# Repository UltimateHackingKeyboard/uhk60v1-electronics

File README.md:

Ultimate Hacking Keyboard electronics
=====================================

Contained are the schematics and board layout KiCad files for the [Ultimate Hacking Keyboard](https://ultimatehackingkeyboard.com/).

Please make sure to clone this repo with:

`git clone --recursive https://github.com/UltimateHackingKeyboard/uhk60v1-electronics.git`

Now, you should be able to open any of the 4 [KiCad](https://kicad.org/) projects of the repo:

* [left-main](left-main) contains main PCB of left keyboard half.
* [right-main](right-main) contains the main PCB of the right keyboard half.
* [display](display) contains the PCB that interfaces our custom manufactured LED segment display with the left main PCB.
* [connectors](connectors) are very small PCBs that are soldered vertically to the left and right main circuit boards to interconnect the keyboard halves without needing a bridge cable.

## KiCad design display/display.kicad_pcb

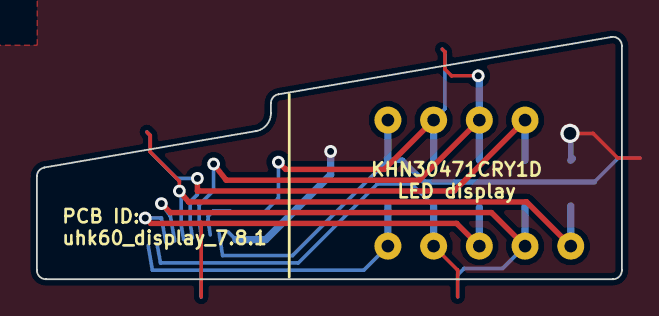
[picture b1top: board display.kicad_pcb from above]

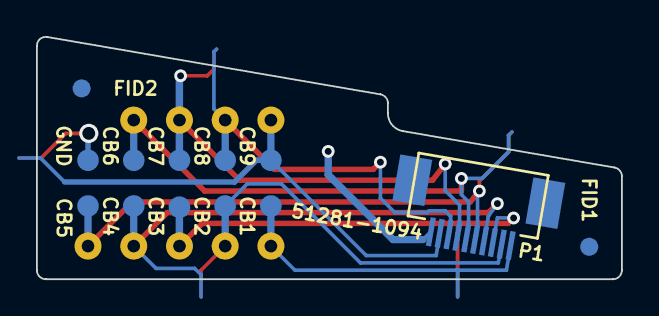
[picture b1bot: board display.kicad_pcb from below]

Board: 2 copper layers, 32.5 x 13.5 mm, 14 parts (13 on the bottom side), 10 nets.

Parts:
FID1, FID2: FIDUCIAL; FID
P1: 51281-1094; FFC_Connector_51281-1094
P2: CONN_9; UHK_LED_display
TP_CB1: CB1; Test_Point
TP_CB2: CB2; Test_Point
TP_CB3: CB3; Test_Point
TP_CB4: CB4; Test_Point
TP_CB5: CB5; Test_Point
TP_CB6: CB6; Test_Point
TP_CB7: CB7; Test_Point
TP_CB8: CB8; Test_Point
TP_CB9: CB9; Test_Point
TP_GND1: GND; Test_Point

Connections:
/CB1: P1.1, P2.1, TP_CB1.1
/CB2: P1.2, P2.2, TP_CB2.1
/CB3: P1.3, P2.3, TP_CB3.1
/CB4: P1.4, P2.4, TP_CB4.1
/CB5: P1.5, P2.5, TP_CB5.1
/CB6: P1.6, P2.6, TP_CB6.1
/CB7: P1.7, P2.7, TP_CB7.1
/CB8: P1.8, P2.8, TP_CB8.1
/CB9: P1.9, P2.9, TP_CB9.1
GND: P1.10, TP_GND1.1

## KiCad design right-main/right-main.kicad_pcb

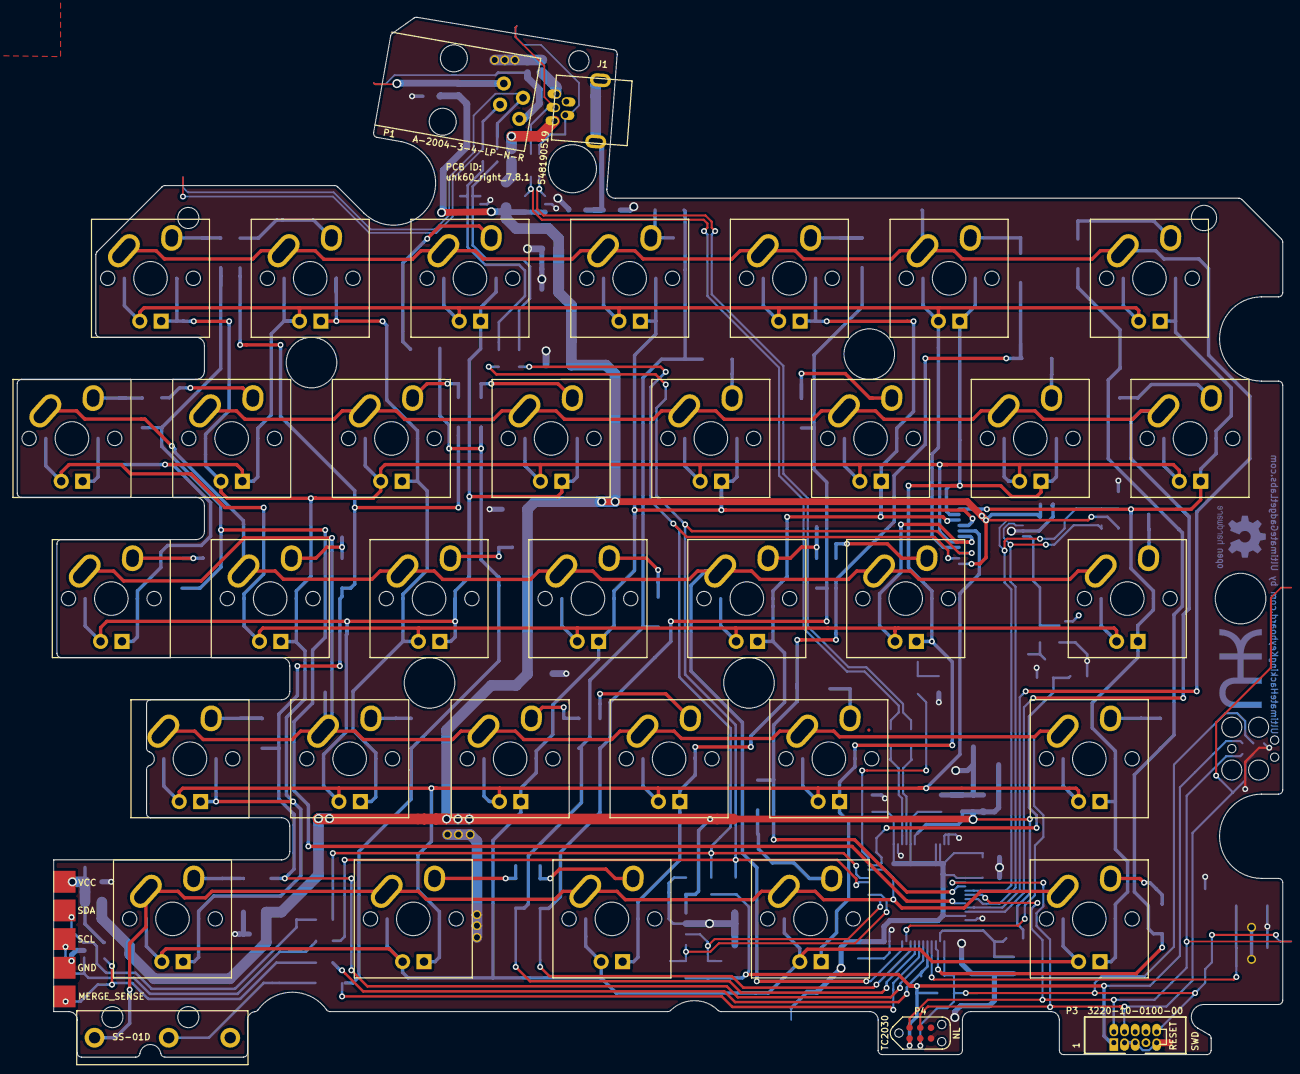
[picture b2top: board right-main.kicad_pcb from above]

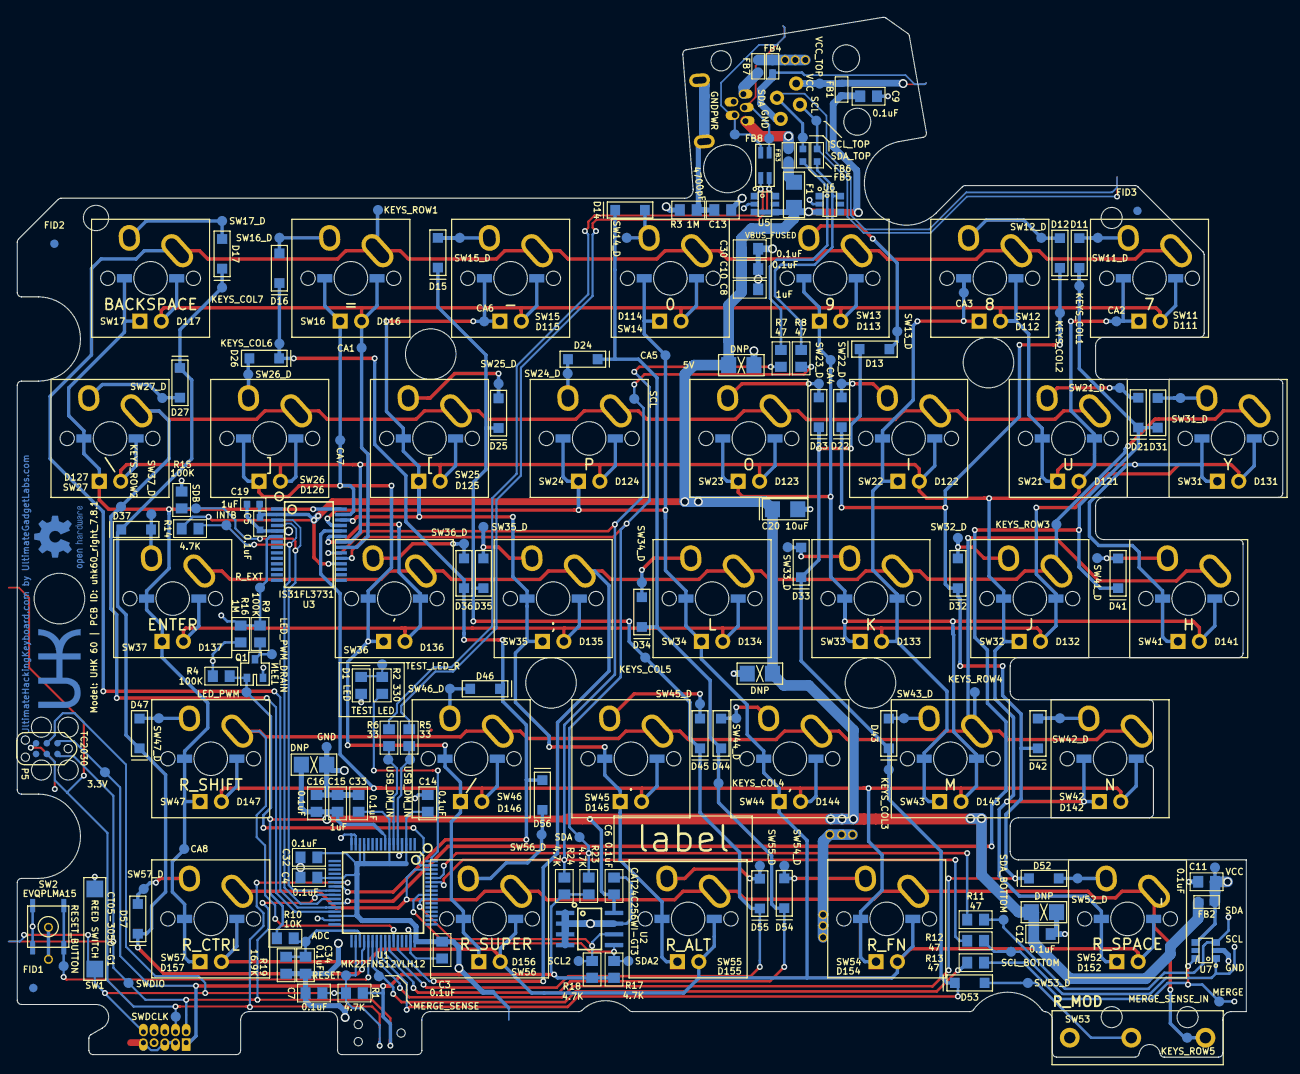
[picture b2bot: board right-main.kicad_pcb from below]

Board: 2 copper layers, 150.1 x 123.4 mm, 285 parts (224 on the bottom side), 94 nets.

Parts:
C3, C4, C6, C7, C9, C10, C11, C12, C14, C16, C30, C32, C33, C34: 0.1uF; SM0805
C5: 0.1uF; SM0603
C8, C15: 1uF; SM0805
C13: 4700pF; SM0805
C19: 1uF; SM0603
C20: 10uF; SM1206_Diode
C22, C23, C24, C25: DNP; SM1206_DNP
D1: LED; SM0805_Diode
D11, D12, D13, D14, D15, D16, D17, D21, D22, D23, D24, D25, D26, D27, D31, D32, D33, D34, D35, D36, D37, D41, D42, D43, D44, D45, D46, D47, D52, D53, D54, D55, D56, D57: DIODE; SOD-123_Diode
D111, D112, D113, D114, D115, D116, D117, D121, D122, D123, D124, D125, D126, D127, D131, D132, D133, D134, D135, D136, D137, D141, D142, D143, D144, D145, D146, D147, D152, D154, D155, D156, D157: LED; Cherry_MX_LED
F1: FUSE; SM1206
FB1, FB2, FB3, FB4, FB5, FB6, FB7: FERRITE_BEAD; SM0603
FB8: FERRITE_BEAD_COMMON_MODE; Wurth_744232090
FID1, FID2, FID3: >VALUE; FID
G1: LOGO; UHK_Logo_5mm_height
G2: LOGO; OSHW_Logo_6mm_height_BCu
GndVia1, GndVia2, GndVia3, GndVia4, GndVia5, GndVia6, GndVia7, GndVia8, GndVia9: VIA; via_28_42mil_solid_con
J1: 548190519; USB_Mini_B_Connector_0548190519
LABEL1: label
P1: A-2004-3-4-LP-N-R; 4P4C_Jack_A-2004-3-4-LP-N-R
P2: CONN_5; UHK_Connector_Right_PCB
P3: 3220-10-0100-00; 2x5_0.05_pitch_pin_shrouded_header_min
P4: CONN_6; Tag_Connect_2x3_Header_No_Legs
P5: CONN_6; Tag_Connect_2x3_Header_With_Legs
Q1: MOSFET_N; SOT-23-GSD
R1, R14, R17, R18, R23, R24: 4.7K; SM0805
R2: 330; SM0805
R3, R16: 1M; SM0805
R4, R9, R15: 100K; SM0805
R5, R6: 33; SM0805
R7, R8, R11, R12, R13: 47; SM0805
R10: 10K; SM0805
R19: 16.9K; SM0805
SW1: CT05-3050-G1; Reed_Switch_CT05-3050-G1
SW2: EVQPLMA15
SW11: 7; Cherry_MX_Matias_Hybrid
SW12: 8; Cherry_MX_Matias_Hybrid
SW13: 9; Cherry_MX_Matias_Hybrid
SW14: 0; Cherry_MX_Matias_Hybrid
SW15: -; Cherry_MX_Matias_Hybrid
SW16: =; Cherry_MX_Matias_Hybrid
SW17: BACKSPACE; Cherry_MX_Matias_Hybrid
SW21: U; Cherry_MX_Matias_Hybrid
SW22: I; Cherry_MX_Matias_Hybrid
SW23: O; Cherry_MX_Matias_Hybrid
SW24: P; Cherry_MX_Matias_Hybrid
SW25: [; Cherry_MX_Matias_Hybrid
SW26: ]; Cherry_MX_Matias_Hybrid
SW27: \; Cherry_MX_Matias_Hybrid
SW31: Y; Cherry_MX_Matias_Hybrid
SW32: J; Cherry_MX_Matias_Hybrid
SW33: K; Cherry_MX_Matias_Hybrid
SW34: L; Cherry_MX_Matias_Hybrid
SW35: ;; Cherry_MX_Matias_Hybrid
SW36: '; Cherry_MX_Matias_Hybrid
SW37: ENTER; Cherry_MX_Matias_Hybrid
SW41: H; Cherry_MX_Matias_Hybrid
SW42: N; Cherry_MX_Matias_Hybrid_Right_Pin
SW43: M; Cherry_MX_Matias_Hybrid
SW44: ,; Cherry_MX_Matias_Hybrid
SW45: .; Cherry_MX_Matias_Hybrid
SW46: /; Cherry_MX_Matias_Hybrid
SW47: R_SHIFT; Cherry_MX_Matias_Hybrid
SW52: R_SPACE; Cherry_MX_Matias_Hybrid
SW53: R_MOD; SS-01D
SW54: R_FN; Cherry_MX_Matias_Hybrid
SW55: R_ALT; Cherry_MX_Matias_Hybrid
SW56: R_SUPER; Cherry_MX_Matias_Hybrid
SW57: R_CTRL; Cherry_MX_Matias_Hybrid
TP_3.3V1: 3.3V; Test_Point
TP_5V1: 5V; Test_Point
TP_ADC1: ADC; Test_Point
TP_CA1: CA1; Test_Point
TP_CA2: CA2; Test_Point
TP_CA3: CA3; Test_Point
TP_CA4: CA4; Test_Point
TP_CA5: CA5; Test_Point
TP_CA6: CA6; Test_Point
TP_CA7: CA7; Test_Point
TP_CA8: CA8; Test_Point
TP_GND1: GND; Test_Point
TP_GNDPWR1: GNDPWR; Test_Point
TP_INTB1: INTB; Test_Point
TP_KEYS_COL1: KEYS_COL1; Test_Point
TP_KEYS_COL2: KEYS_COL2; Test_Point
TP_KEYS_COL3: KEYS_COL3; Test_Point
TP_KEYS_COL4: KEYS_COL4; Test_Point
TP_KEYS_COL5: KEYS_COL5; Test_Point
TP_KEYS_COL6: KEYS_COL6; Test_Point
TP_KEYS_COL7: KEYS_COL7; Test_Point
TP_KEYS_ROW1: KEYS_ROW1; Test_Point
TP_KEYS_ROW2: KEYS_ROW2; Test_Point
TP_KEYS_ROW3: KEYS_ROW3; Test_Point
TP_KEYS_ROW4: KEYS_ROW4; Test_Point
TP_KEYS_ROW5: KEYS_ROW5; Test_Point
TP_LED_PWM1: LED_PWM; Test_Point
TP_LED_PWM_DRAIN1: LED_PWM_DRAIN; Test_Point
TP_MERGE_SENSE1: MERGE_SENSE; Test_Point
TP_MERGE_SENSE_IN1: MERGE_SENSE_IN; Test_Point
TP_RESET1: RESET; Test_Point
TP_RESET_BUTTON1: RESET_BUTTON; Test_Point
TP_R_EXT1: R_EXT; Test_Point
TP_SCL1: SCL; Test_Point
TP_SCL2: SCL2; Test_Point
TP_SCL_BOTTOM1: SCL_BOTTOM; Test_Point
TP_SCL_TOP1: SCL_TOP; Test_Point
TP_SDA1: SDA; Test_Point
TP_SDA2: SDA2; Test_Point
TP_SDA_BOTTOM1: SDA_BOTTOM; Test_Point
TP_SDA_TOP1: SDA_TOP; Test_Point
TP_SDB1: SDB; Test_Point
TP_SW11_D1: SW11_D; Test_Point
TP_SW12_D1: SW12_D; Test_Point
TP_SW13_D1: SW13_D; Test_Point
TP_SW14_D1: SW14_D; Test_Point
TP_SW15_D1: SW15_D; Test_Point
TP_SW16_D1: SW16_D; Test_Point
TP_SW17_D1: SW17_D; Test_Point
TP_SW21_D1: SW21_D; Test_Point
TP_SW22_D1: SW22_D; Test_Point
TP_SW23_D1: SW23_D; Test_Point
TP_SW24_D1: SW24_D; Test_Point
TP_SW25_D1: SW25_D; Test_Point
TP_SW26_D1: SW26_D; Test_Point
TP_SW27_D1: SW27_D; Test_Point
TP_SW31_D1: SW31_D; Test_Point
TP_SW32_D1: SW32_D; Test_Point
TP_SW33_D1: SW33_D; Test_Point
TP_SW34_D1: SW34_D; Test_Point
TP_SW35_D1: SW35_D; Test_Point
TP_SW36_D1: SW36_D; Test_Point
TP_SW37_D1: SW37_D; Test_Point
TP_SW41_D1: SW41_D; Test_Point
TP_SW42_D1: SW42_D; Test_Point
TP_SW43_D1: SW43_D; Test_Point
TP_SW44_D1: SW44_D; Test_Point
TP_SW45_D1: SW45_D; Test_Point
TP_SW46_D1: SW46_D; Test_Point
TP_SW47_D1: SW47_D; Test_Point
TP_SW52_D1: SW52_D; Test_Point
TP_SW53_D1: SW53_D; Test_Point
TP_SW54_D1: SW54_D; Test_Point
TP_SW55_D1: SW55_D; Test_Point
TP_SW56_D1: SW56_D; Test_Point
TP_SW57_D1: SW57_D; Test_Point
TP_SWDCLK1: SWDCLK; Test_Point
TP_SWDIO1: SWDIO; Test_Point
TP_TEST_LED_R1: TEST_LED_R; Test_Point
TP_USB_DM1: USB_DM_IN; Test_Point
TP_USB_DM_IN1: USB_DM_IN; Test_Point
TP_USB_DP1: USB_DM_IN; Test_Point
TP_USB_DP_IN1: USB_DP_IN; Test_Point
TP_VBUS_FUSED1: VBUS_FUSED; Test_Point
TP_VCC_BOTTOM1: VCC_BOTTOM; Test_Point
TP_VCC_TOP1: VCC_TOP; Test_Point
U1: MK22FN512VLH12; LQFP64
U2: CAT24C256WI-GT3; EEPROM-SOIC8
U3: IS31FL3731; SSOP-28
U5, U6, U7: ESD; SC-74-TVS
VIA1, VIA2: via_28_42mil_solid_con
hole: 2.6mm; hole_2.4mm
hole#2, hole#3, hole#4, hole#5, hole#6: 6mm; hole_6mm
hole#7: 5.7mm; hole_5.7mm
hole#8, hole#10, hole#11: 2.5mm; hole_2.5mm
hole#9: 3mm; hole_3mm

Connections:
+3V3: C3.2, C4.1, C14.2, C32.2, C33.2, P3.1, P4.1, P5.1, R1.1, R17.1, R18.1, R23.1, R24.1, TP_3.3V1.1, U1.3, U1.7, U1.13, U1.14, U1.21, U1.30, U1.48
+5V: C5.2, C6.2, C8.2, C9.2, C10.2, C12.2, C15.2, C16.2, C19.2, C20.1, C22.2, C23.2, C24.2, C25.2, C30.2, F1.1, FB1.2, FB2.2, R10.1, R14.1, TP_5V1.1, TP_VBUS_FUSED1.1, U1.8, U2.8, U3.2, U3.18, U5.3, U5.4, U6.3
/ADC: C34.2, R10.2, R19.1, TP_ADC1.1, U1.35
/CA1: D111.2, D112.2, D113.2, D114.2, D115.2, D116.2, D117.2, D121.1, D131.1, D141.1, TP_CA1.1, U3.21
/CA2: D111.1, D121.2, D122.2, D123.2, D124.2, D125.2, D126.2, D127.2, D132.1, D142.1, D152.1, TP_CA2.1, U3.22
/CA3: D112.1, D122.1, D131.2, D132.2, D133.2, D134.2, D135.2, D136.2, D137.2, D143.1, TP_CA3.1, U3.23
/CA4: D113.1, D123.1, D133.1, D141.2, D142.2, D143.2, D144.2, D145.2, D146.2, D147.2, D154.1, TP_CA4.1, U3.24
/CA5: D114.1, D124.1, D134.1, D144.1, D152.2, D154.2, D155.2, D156.2, D157.2, TP_CA5.1, U3.25
/CA6: D115.1, D125.1, D135.1, D145.1, D155.1, TP_CA6.1, U3.26
/CA7: D116.1, D126.1, D136.1, D146.1, D156.1, TP_CA7.1, U3.27
/CA8: D117.1, D127.1, D137.1, D147.1, D157.1, TP_CA8.1, U3.28
/GND_IN: FB7.1, J1.4
/GND_TOP: FB4.1, P1.1
/INTB: R14.2, TP_INTB1.1, U1.26, U3.4
/KEYS_COL1: D11.2, D21.2, D31.2, D41.2, TP_KEYS_COL1.1, U1.27
/KEYS_COL2: D12.2, D22.2, D32.2, D42.2, D52.2, TP_KEYS_COL2.1, U1.39
/KEYS_COL3: D13.2, D23.2, D33.2, D43.2, D53.2, TP_KEYS_COL3.1, U1.40
/KEYS_COL4: D14.2, D24.2, D34.2, D44.2, D54.2, TP_KEYS_COL4.1, U1.41
/KEYS_COL5: D15.2, D25.2, D35.2, D45.2, D55.2, TP_KEYS_COL5.1, U1.42
/KEYS_COL6: D16.2, D26.2, D36.2, D46.2, D56.2, TP_KEYS_COL6.1, U1.23
/KEYS_COL7: D17.2, D27.2, D37.2, D47.2, D57.2, TP_KEYS_COL7.1, U1.36
/KEYS_ROW1: SW11.1, SW12.1, SW13.1, SW14.1, SW15.1, SW16.1, SW17.1, TP_KEYS_ROW1.1, U1.28
/KEYS_ROW2: SW21.1, SW22.1, SW23.1, SW24.1, SW25.1, SW26.1, SW27.1, TP_KEYS_ROW2.1, U1.29
/KEYS_ROW3: SW31.1, SW32.1, SW33.1, SW34.1, SW35.1, SW36.1, SW37.1, TP_KEYS_ROW3.1, U1.44
/KEYS_ROW4: SW41.1, SW42.1, SW43.1, SW44.1, SW45.1, SW46.1, SW47.1, TP_KEYS_ROW4.1, U1.43
/KEYS_ROW5: SW52.1, SW53.1, SW54.1, SW55.1, SW56.1, SW57.1, TP_KEYS_ROW5.1, U1.62
/LED_PWM: Q1.G, R4.2, TP_LED_PWM1.1, U1.63
/LED_PWM_DRAIN: Q1.D, R9.2, TP_LED_PWM_DRAIN1.1
/MERGE_SENSE: R13.1, TP_MERGE_SENSE1.1, U1.38
/MERGE_SENSE_IN: P2.5, R13.2, TP_MERGE_SENSE_IN1.1, U7.5
/RESET: C7.2, P3.10, P4.3, P5.3, R1.2, SW1.1, TP_RESET1.1, U1.34
/RESET_BUTTON: SW2.2, TP_RESET_BUTTON1.1, U1.37
/R_EXT: R9.1, R16.1, TP_R_EXT1.1, U3.6
/SCL: R8.1, R12.1, R24.2, TP_SCL1.1, U1.59, U3.20
/SCL2: R18.2, TP_SCL2.1, U1.55, U2.6
/SCL_BOTTOM: P2.3, R12.2, TP_SCL_BOTTOM1.1, U7.1
/SCL_MID: FB6.2, R8.2, U6.5
/SCL_TOP: FB6.1, P1.2, TP_SCL_TOP1.1
/SDA: R7.1, R11.1, R23.2, TP_SDA1.1, U1.60, U3.19
/SDA2: R17.2, TP_SDA2.1, U1.56, U2.5
/SDA_BOTTOM: P2.2, R11.2, TP_SDA_BOTTOM1.1, U7.3
/SDA_MID: FB5.2, R7.2, U6.1
/SDA_TOP: FB5.1, P1.3, TP_SDA_TOP1.1
/SDB: R15.1, TP_SDB1.1, U1.24, U3.3
/SW11_D: D11.1, SW11.2, TP_SW11_D1.1
/SW12_D: D12.1, SW12.2, TP_SW12_D1.1
/SW13_D: D13.1, SW13.2, TP_SW13_D1.1
/SW14_D: D14.1, SW14.2, TP_SW14_D1.1
/SW15_D: D15.1, SW15.2, TP_SW15_D1.1
/SW16_D: D16.1, SW16.2, TP_SW16_D1.1
/SW17_D: D17.1, SW17.2, TP_SW17_D1.1
/SW21_D: D21.1, SW21.2, TP_SW21_D1.1
/SW22_D: D22.1, SW22.2, TP_SW22_D1.1
/SW23_D: D23.1, SW23.2, TP_SW23_D1.1
/SW24_D: D24.1, SW24.2, TP_SW24_D1.1
/SW25_D: D25.1, SW25.2, TP_SW25_D1.1
/SW26_D: D26.1, SW26.2, TP_SW26_D1.1
/SW27_D: D27.1, SW27.2, TP_SW27_D1.1
/SW31_D: D31.1, SW31.2, TP_SW31_D1.1
/SW32_D: D32.1, SW32.2, TP_SW32_D1.1
/SW33_D: D33.1, SW33.2, TP_SW33_D1.1
/SW34_D: D34.1, SW34.2, TP_SW34_D1.1
/SW35_D: D35.1, SW35.2, TP_SW35_D1.1
/SW36_D: D36.1, SW36.2, TP_SW36_D1.1
/SW37_D: D37.1, SW37.2, TP_SW37_D1.1
/SW41_D: D41.1, SW41.2, TP_SW41_D1.1
/SW42_D: D42.1, SW42.2, TP_SW42_D1.1
/SW43_D: D43.1, SW43.2, TP_SW43_D1.1
/SW44_D: D44.1, SW44.2, TP_SW44_D1.1
/SW45_D: D45.1, SW45.2, TP_SW45_D1.1
/SW46_D: D46.1, SW46.2, TP_SW46_D1.1
/SW47_D: D47.1, SW47.2, TP_SW47_D1.1
/SW52_D: D52.1, SW52.2, TP_SW52_D1.1
/SW53_D: D53.1, SW53.2, TP_SW53_D1.1
/SW54_D: D54.1, SW54.2, TP_SW54_D1.1
/SW55_D: D55.1, SW55.2, TP_SW55_D1.1
/SW56_D: D56.1, SW56.2, TP_SW56_D1.1
/SW57_D: D57.1, SW57.2, TP_SW57_D1.1
/SWDCLK: P3.4, P4.4, P5.4, TP_SWDCLK1.1, U1.22
/SWDIO: P3.2, P4.2, P5.2, TP_SWDIO1.1, U1.25
/TEST_LED_R: D1.2, R2.2, TP_TEST_LED_R1.1
/USB_D+: R5.1, TP_USB_DP1.1, U1.5
/USB_D-: R6.1, TP_USB_DM1.1, U1.6
/USB_D_IN+: FB8.4, J1.3, TP_USB_DP_IN1.1
/USB_D_IN-: FB8.1, J1.2, TP_USB_DM_IN1.1
/USB_D_MID+: FB8.3, R5.2, U5.5
/USB_D_MID-: FB8.2, R6.2, U5.1
/VBUS: FB3.1, J1.1
/VBUS_MID: F1.2, FB3.2
/VCC_BOTTOM: C11.2, FB2.1, P2.1, TP_VCC_BOTTOM1.1, U7.4
/VCC_TOP: FB1.1, P1.4, TP_VCC_TOP1.1
GND: C3.1, C4.2, C5.1, C6.1, C7.1, C8.1, C9.1, C10.1, C11.1, C12.1, C13.2, C14.1, C15.1, C16.1, C19.1, C20.2, C22.1, C23.1, C24.1, C25.1, C30.1, C32.1, C33.1, C34.1, D1.1, FB4.2, FB7.2, GndVia1.1, GndVia2.1, GndVia3.1, GndVia4.1, GndVia5.1, GndVia6.1, GndVia7.1, GndVia8.1, GndVia9.1, P2.4, P3.3, P3.5, P3.9, P4.5, P5.5, Q1.S, R3.1, R4.1, R15.2, R16.2, R19.2, SW1.2, SW2.1, TP_GND1.1, U1.4, U1.15, U1.16, U1.31, U1.47, U2.1, U2.2, U2.3, U2.4, U2.7, U3.5, U5.2, U6.2, U7.2
GNDPWR: C13.1, J1.5, R3.2, TP_GNDPWR1.1
unnamed: R2.1, U1.64

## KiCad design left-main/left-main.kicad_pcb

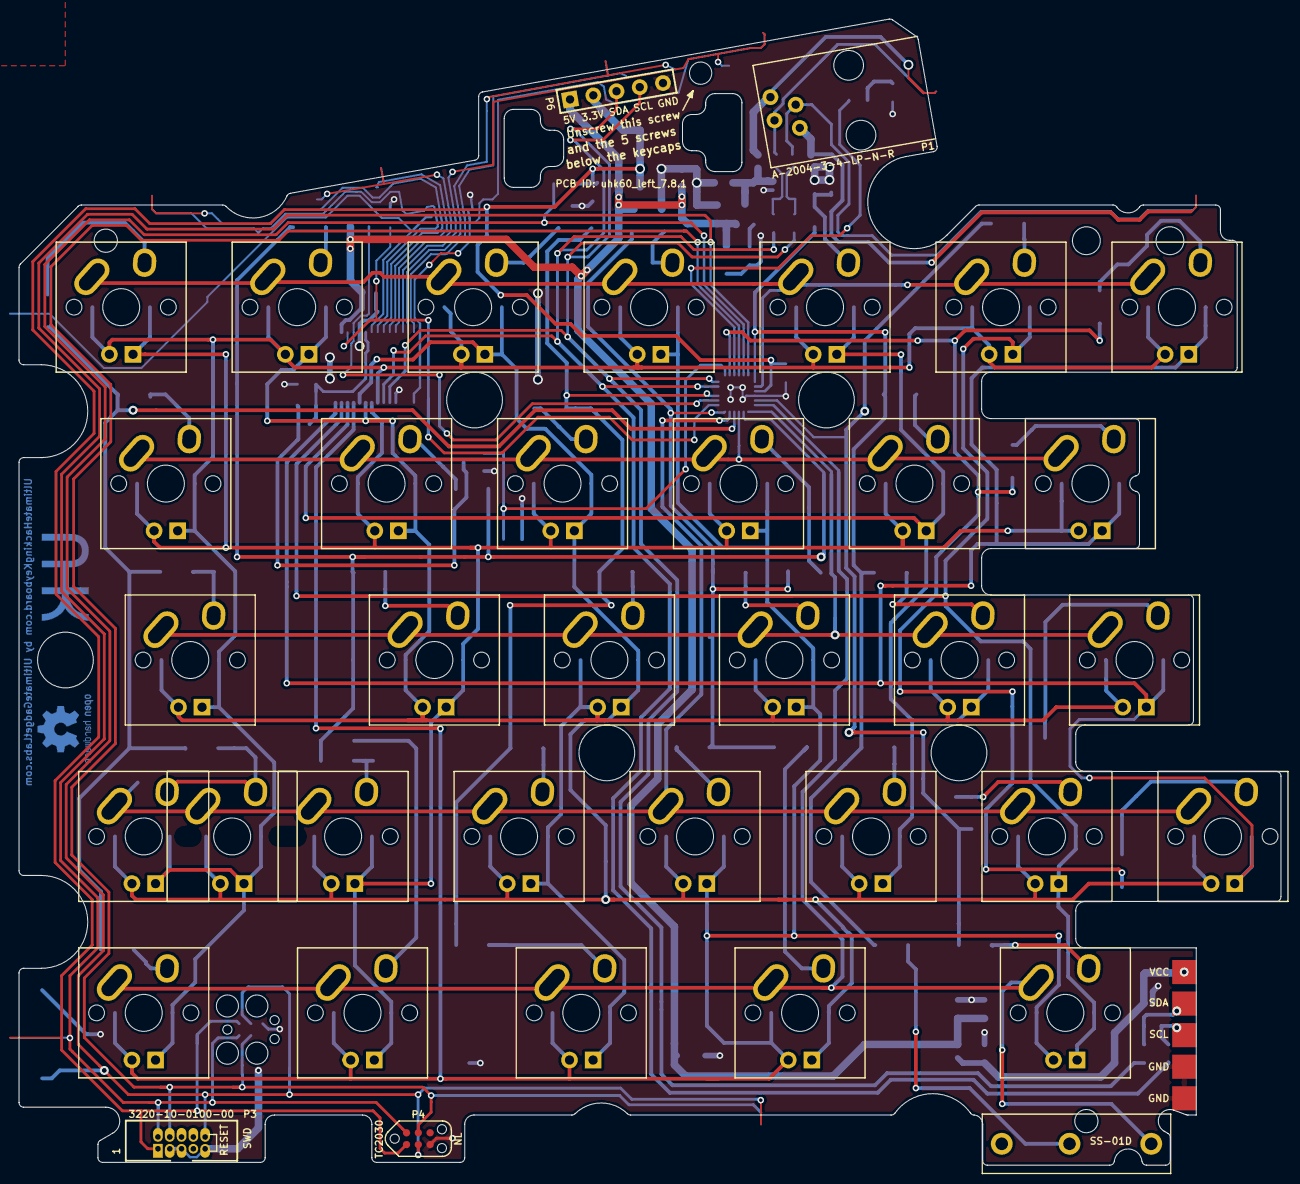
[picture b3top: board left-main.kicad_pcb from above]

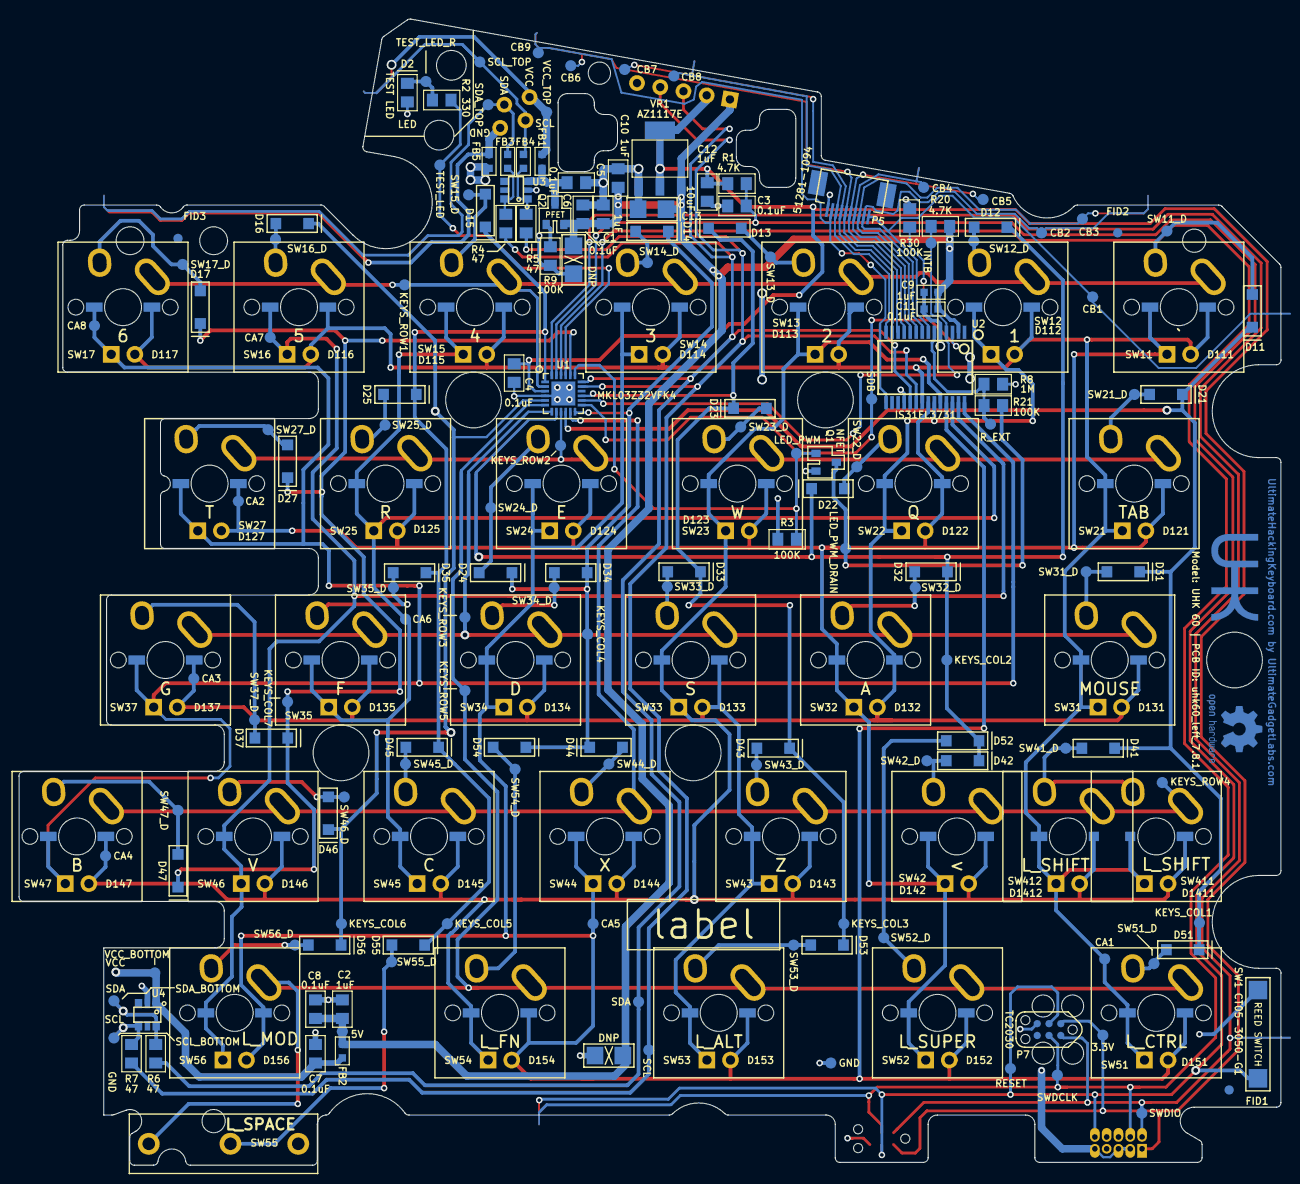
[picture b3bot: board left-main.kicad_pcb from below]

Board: 2 copper layers, 135.9 x 123.4 mm, 243 parts (195 on the bottom side), 87 nets.

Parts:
C1, C2, C10, C12: 1uF; SM0805
C3, C4, C5, C6, C7, C8: 0.1uF; SM0805
C9: 1uF; SM0603
C11: 0.1uF; SM0603
C13: 10uF; SM1206_Diode
C21, C24: DNP; SM1206_DNP
D2: LED; SM0805_Diode
D11, D12, D13, D14, D15, D16, D17, D21, D22, D23, D24, D25, D27, D31, D32, D33, D34, D35, D37, D41, D42, D43, D44, D45, D46, D47, D51, D52, D53, D54, D55, D56: DIODE; SOD-123_Diode
D111, D112, D113, D114, D115, D116, D117, D121, D122, D123, D124, D125, D127, D131, D132, D133, D134, D135, D137, D142, D143, D144, D145, D146, D147, D151, D152, D153, D154, D156: LED; Cherry_MX_LED
D1411: LED; Cherry_MX_LED_ISO_Shift
D1412: LED; Cherry_MX_LED_ANSI_Shift
FB1, FB2, FB3, FB4, FB5: FERRITE_BEAD; SM0603
FID1, FID2, FID3: FIDUCIAL; FID
G1: LOGO; UHK_Logo_5mm_height
G2: LOGO; OSHW_Logo_6mm_height_BCu
LABEL1: label
P1: A-2004-3-4-LP-N-R; 4P4C_Jack_A-2004-3-4-LP-N-R
P2: CONN_5; UHK_Connector_Left_PCB
P3: 3220-10-0100-00; 2x5_0.05_pitch_pin_shrouded_header_min
P4: CONN_6; Tag_Connect_2x3_Header_No_Legs
P5: 51281-1094; FFC_Connector_51281-1094
P6: CONN_5; 1x5_pin_unshrouded_header
P7: CONN_6; Tag_Connect_2x3_Header_With_Legs
Q1: MOSFET_N; SOT-23-GSD
Q2: MOSFET_P; SOT-23-GSD
R1, R20: 4.7K; SM0805
R2: 330; SM0805
R3, R9, R21, R30: 100K; SM0805
R4, R5, R6, R7: 47; SM0805
R8: 1M; SM0805
SW1: CT05-3050-G1; Reed_Switch_CT05-3050-G1
SW11: `; Cherry_MX_Matias_Hybrid
SW12: 1; Cherry_MX_Matias_Hybrid
SW13: 2; Cherry_MX_Matias_Hybrid
SW14: 3; Cherry_MX_Matias_Hybrid
SW15: 4; Cherry_MX_Matias_Hybrid
SW16: 5; Cherry_MX_Matias_Hybrid
SW17: 6; Cherry_MX_Matias_Hybrid
SW21: TAB; Cherry_MX_Matias_Hybrid
SW22: Q; Cherry_MX_Matias_Hybrid
SW23: W; Cherry_MX_Matias_Hybrid
SW24: E; Cherry_MX_Matias_Hybrid
SW25: R; Cherry_MX_Matias_Hybrid
SW27: T; Cherry_MX_Matias_Hybrid_Left_Pin
SW31: MOUSE; Cherry_MX_Matias_Hybrid
SW32: A; Cherry_MX_Matias_Hybrid
SW33: S; Cherry_MX_Matias_Hybrid
SW34: D; Cherry_MX_Matias_Hybrid
SW35: F; Cherry_MX_Matias_Hybrid
SW37: G; Cherry_MX_Matias_Hybrid
SW42: <; Cherry_MX_Matias_Hybrid_Right_Pin
SW43: Z; Cherry_MX_Matias_Hybrid
SW44: X; Cherry_MX_Matias_Hybrid
SW45: C; Cherry_MX_Matias_Hybrid
SW46: V; Cherry_MX_Matias_Hybrid
SW47: B; Cherry_MX_Matias_Hybrid
SW51: L_CTRL; Cherry_MX_Matias_Hybrid
SW52: L_SUPER; Cherry_MX_Matias_Hybrid
SW53: L_ALT; Cherry_MX_Matias_Hybrid
SW54: L_FN; Cherry_MX_Matias_Hybrid
SW55: L_SPACE; SS-01D
SW56: L_MOD; Cherry_MX_Matias_Hybrid
SW411: L_SHIFT; Cherry_MX_Matias_Hybrid_Left_Pin
SW412: L_SHIFT; Cherry_MX_Matias_Hybrid_ANSI_Shift
TP_3.3V1: 3.3V; Test_Point
TP_5V1: 5V; Test_Point
TP_CA1: CA1; Test_Point
TP_CA2: CA2; Test_Point
TP_CA3: CA3; Test_Point
TP_CA4: CA4; Test_Point
TP_CA5: CA5; Test_Point
TP_CA6: CA6; Test_Point
TP_CA7: CA7; Test_Point
TP_CA8: CA8; Test_Point
TP_CB1: CB1; Test_Point
TP_CB2: CB2; Test_Point
TP_CB3: CB3; Test_Point
TP_CB4: CB4; Test_Point
TP_CB5: CB5; Test_Point
TP_CB6: CB6; Test_Point
TP_CB7: CB7; Test_Point
TP_CB8: CB8; Test_Point
TP_CB9: CB9; Test_Point
TP_GND1: GND; Test_Point
TP_INTB1: INTB; Test_Point
TP_KEYS_COL1: KEYS_COL1; Test_Point
TP_KEYS_COL2: KEYS_COL2; Test_Point
TP_KEYS_COL3: KEYS_COL3; Test_Point
TP_KEYS_COL4: KEYS_COL4; Test_Point
TP_KEYS_COL5: KEYS_COL5; Test_Point
TP_KEYS_COL6: KEYS_COL6; Test_Point
TP_KEYS_COL7: KEYS_COL7; Test_Point
TP_KEYS_ROW1: KEYS_ROW1; Test_Point
TP_KEYS_ROW2: KEYS_ROW2; Test_Point
TP_KEYS_ROW3: KEYS_ROW3; Test_Point
TP_KEYS_ROW4: KEYS_ROW4; Test_Point
TP_KEYS_ROW5: KEYS_ROW5; Test_Point
TP_LED_PWM1: LED_PWM; Test_Point
TP_LED_PWM_DRAIN1: LED_PWM_DRAIN; Test_Point
TP_RESET1: RESET; Test_Point
TP_R_EXT1: R_EXT; Test_Point
TP_SCL1: SCL; Test_Point
TP_SCL_BOTTOM1: SCL_BOTTOM; Test_Point
TP_SCL_TOP1: SCL_TOP; Test_Point
TP_SDA1: SDA; Test_Point
TP_SDA_BOTTOM1: SDA_BOTTOM; Test_Point
TP_SDA_TOP1: SDA_TOP; Test_Point
TP_SDB1: SDB; Test_Point
TP_SW11_D1: SW11_D; Test_Point
TP_SW12_D1: SW12_D; Test_Point
TP_SW13_D1: SW13_D; Test_Point
TP_SW14_D1: SW14_D; Test_Point
TP_SW15_D1: SW15_D; Test_Point
TP_SW16_D1: SW16_D; Test_Point
TP_SW17_D1: SW17_D; Test_Point
TP_SW21_D1: SW21_D; Test_Point
TP_SW22_D1: SW22_D; Test_Point
TP_SW23_D1: SW23_D; Test_Point
TP_SW24_D1: SW24_D; Test_Point
TP_SW25_D1: SW25_D; Test_Point
TP_SW27_D1: SW27_D; Test_Point
TP_SW31_D1: SW31_D; Test_Point
TP_SW32_D1: SW32_D; Test_Point
TP_SW33_D1: SW33_D; Test_Point
TP_SW34_D1: SW34_D; Test_Point
TP_SW35_D1: SW35_D; Test_Point
TP_SW37_D1: SW37_D; Test_Point
TP_SW41_D1: SW41_D; Test_Point
TP_SW42_D1: SW42_D; Test_Point
TP_SW43_D1: SW43_D; Test_Point
TP_SW44_D1: SW44_D; Test_Point
TP_SW45_D1: SW45_D; Test_Point
TP_SW46_D1: SW46_D; Test_Point
TP_SW47_D1: SW47_D; Test_Point
TP_SW51_D1: SW51_D; Test_Point
TP_SW52_D1: SW52_D; Test_Point
TP_SW53_D1: SW53_D; Test_Point
TP_SW54_D1: SW54_D; Test_Point
TP_SW55_D1: SW55_D; Test_Point
TP_SW56_D1: SW56_D; Test_Point
TP_SWDCLK1: SWDCLK; Test_Point
TP_SWDIO1: SWDIO; Test_Point
TP_TEST_LED1: TEST_LED; Test_Point
TP_TEST_LED_R1: TEST_LED_R; Test_Point
TP_VCC_BOTTOM1: VCC_BOTTOM; Test_Point
TP_VCC_TOP1: VCC_TOP; Test_Point
U1: MKL03Z32VFK4; QFN-24-1EP_4x4mm_Pitch0.5mm
U2: IS31FL3731; SSOP-28
U3, U4: ESD; SC-74-TVS
VR1: AZ1117E; SOT-223
hole: 2.6mm; hole_2.4mm
hole#2, hole#3, hole#4, hole#5, hole#6: 6mm; hole_6mm
hole#7, hole#10: 2.5mm; hole_2.5mm
hole#8, hole#9: 3mm; hole_3mm

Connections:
+3V3: C4.2, C12.2, P3.1, P4.1, P6.2, P7.1, R1.1, TP_3.3V1.1, U1.3, VR1.2
+5V: C1.2, C2.2, C6.2, C8.2, C9.2, C10.2, C11.2, C13.1, C21.2, C24.2, FB2.2, P6.1, Q2.S, R20.1, TP_5V1.1, U2.2, VR1.3
/CA1: D111.2, D112.2, D113.2, D114.2, D115.2, D116.2, D117.2, D121.1, D131.1, D151.1, D1411.1, D1412.1, TP_CA1.1, U2.21
/CA2: D111.1, D121.2, D122.2, D123.2, D124.2, D125.2, D127.2, D132.1, D142.1, D152.1, TP_CA2.1, U2.22
/CA3: D112.1, D122.1, D131.2, D132.2, D133.2, D134.2, D135.2, D137.2, D143.1, D153.1, TP_CA3.1, U2.23
/CA4: D113.1, D123.1, D133.1, D142.2, D143.2, D144.2, D145.2, D146.2, D147.2, D154.1, D1411.2, D1412.2, TP_CA4.1, U2.24
/CA5: D114.1, D124.1, D134.1, D144.1, D151.2, D152.2, D153.2, D154.2, D156.2, TP_CA5.1, U2.25
/CA6: D115.1, D125.1, D135.1, D145.1, TP_CA6.1, U2.26
/CA7: D116.1, D146.1, D156.1, TP_CA7.1, U2.27
/CA8: D117.1, D127.1, D137.1, D147.1, TP_CA8.1, U2.28
/CB1: P5.1, TP_CB1.1, U2.7
/CB2: P5.2, TP_CB2.1, U2.8
/CB3: P5.3, TP_CB3.1, U2.9
/CB4: P5.4, TP_CB4.1, U2.10
/CB5: P5.5, TP_CB5.1, U2.11
/CB6: P5.6, TP_CB6.1, U2.12
/CB7: P5.7, TP_CB7.1, U2.13
/CB8: P5.8, TP_CB8.1, U2.14
/CB9: P5.9, TP_CB9.1, U2.15
/GND_TOP: FB5.1, P1.4
/INTB: R20.2, TP_INTB1.1, U1.14, U2.4
/KEYS_COL1: D11.2, D21.2, D31.2, D41.2, D51.2, TP_KEYS_COL1.1, U1.10
/KEYS_COL2: D12.2, D22.2, D32.2, D42.2, D52.2, TP_KEYS_COL2.1, U1.8
/KEYS_COL3: D13.2, D23.2, D33.2, D43.2, D53.2, TP_KEYS_COL3.1, U1.15
/KEYS_COL4: D14.2, D24.2, D34.2, D44.2, D54.2, TP_KEYS_COL4.1, U1.12
/KEYS_COL5: D15.2, D25.2, D35.2, D45.2, D55.2, TP_KEYS_COL5.1, U1.1
/KEYS_COL6: D16.2, D46.2, D56.2, TP_KEYS_COL6.1, U1.5
/KEYS_COL7: D17.2, D27.2, D37.2, D47.2, TP_KEYS_COL7.1, U1.20
/KEYS_ROW1: SW11.1, SW12.1, SW13.1, SW14.1, SW15.1, SW16.1, SW17.1, TP_KEYS_ROW1.1, U1.2
/KEYS_ROW2: SW21.1, SW22.1, SW23.1, SW24.1, SW25.1, SW27.1, TP_KEYS_ROW2.1, U1.9
/KEYS_ROW3: SW31.1, SW32.1, SW33.1, SW34.1, SW35.1, SW37.1, TP_KEYS_ROW3.1, U1.7
/KEYS_ROW4: SW42.1, SW43.1, SW44.1, SW45.1, SW46.1, SW47.1, SW411.1, SW412.1, TP_KEYS_ROW4.1, U1.11
/KEYS_ROW5: SW51.1, SW52.1, SW53.1, SW54.1, SW55.1, SW56.1, TP_KEYS_ROW5.1, U1.6
/LED_PWM: Q1.G, R3.2, TP_LED_PWM1.1, U1.19
/LED_PWM_DRAIN: Q1.D, R21.2, TP_LED_PWM_DRAIN1.1
/PFET_DRAIN: C5.2, FB1.2, Q2.D, U3.3
/PFET_G: Q2.G, R9.1
/RESET: C3.2, P3.10, P4.3, P7.3, R1.2, SW1.2, TP_RESET1.1, U1.23
/R_EXT: R8.2, R21.1, TP_R_EXT1.1, U2.6
/SCL: P6.4, R5.1, R7.1, TP_SCL1.1, U1.17, U2.20
/SCL_BOTTOM: P2.3, R7.2, TP_SCL_BOTTOM1.1, U4.4
/SCL_MID: FB4.2, R5.2, U3.1
/SCL_TOP: FB4.1, P1.3, TP_SCL_TOP1.1
/SDA: P6.3, R4.1, R6.1, TP_SDA1.1, U1.18, U2.19
/SDA_BOTTOM: P2.2, R6.2, TP_SDA_BOTTOM1.1, U4.5
/SDA_MID: FB3.2, R4.2, U3.5
/SDA_TOP: FB3.1, P1.2, TP_SDA_TOP1.1
/SDB: R30.1, TP_SDB1.1, U1.13, U2.3
/SW11_D: D11.1, SW11.2, TP_SW11_D1.1
/SW12_D: D12.1, SW12.2, TP_SW12_D1.1
/SW13_D: D13.1, SW13.2, TP_SW13_D1.1
/SW14_D: D14.1, SW14.2, TP_SW14_D1.1
/SW15_D: D15.1, SW15.2, TP_SW15_D1.1
/SW16_D: D16.1, SW16.2, TP_SW16_D1.1
/SW17_D: D17.1, SW17.2, TP_SW17_D1.1
/SW21_D: D21.1, SW21.2, TP_SW21_D1.1
/SW22_D: D22.1, SW22.2, TP_SW22_D1.1
/SW23_D: D23.1, SW23.2, TP_SW23_D1.1
/SW24_D: D24.1, SW24.2, TP_SW24_D1.1
/SW25_D: D25.1, SW25.2, TP_SW25_D1.1
/SW27_D: D27.1, SW27.2, TP_SW27_D1.1
/SW31_D: D31.1, SW31.2, TP_SW31_D1.1
/SW32_D: D32.1, SW32.2, TP_SW32_D1.1
/SW33_D: D33.1, SW33.2, TP_SW33_D1.1
/SW34_D: D34.1, SW34.2, TP_SW34_D1.1
/SW35_D: D35.1, SW35.2, TP_SW35_D1.1
/SW37_D: D37.1, SW37.2, TP_SW37_D1.1
/SW41_D: D41.1, SW411.2, SW412.2, TP_SW41_D1.1
/SW42_D: D42.1, SW42.2, TP_SW42_D1.1
/SW43_D: D43.1, SW43.2, TP_SW43_D1.1
/SW44_D: D44.1, SW44.2, TP_SW44_D1.1
/SW45_D: D45.1, SW45.2, TP_SW45_D1.1
/SW46_D: D46.1, SW46.2, TP_SW46_D1.1
/SW47_D: D47.1, SW47.2, TP_SW47_D1.1
/SW51_D: D51.1, SW51.2, TP_SW51_D1.1
/SW52_D: D52.1, SW52.2, TP_SW52_D1.1
/SW53_D: D53.1, SW53.2, TP_SW53_D1.1
/SW54_D: D54.1, SW54.2, TP_SW54_D1.1
/SW55_D: D55.1, SW55.2, TP_SW55_D1.1
/SW56_D: D56.1, SW56.2, TP_SW56_D1.1
/SWDCLK: P3.4, P4.4, P7.4, TP_SWDCLK1.1, U1.22
/SWDIO: P3.2, P4.2, P7.2, TP_SWDIO1.1, U1.24
/TEST_LED: R2.2, TP_TEST_LED1.1, U1.21
/TEST_LED_R: D2.2, R2.1, TP_TEST_LED_R1.1
/VCC_BOTTOM: C7.2, FB2.1, P2.1, TP_VCC_BOTTOM1.1, U4.1
/VCC_TOP: FB1.1, P1.1, TP_VCC_TOP1.1
GND: C1.1, C2.1, C3.1, C4.1, C5.1, C6.1, C7.1, C8.1, C9.1, C10.1, C11.1, C12.1, C13.2, C21.1, C24.1, D2.1, FB5.2, P2.4, P2.5, P3.3, P3.5, P3.9, P4.5, P5.10, P6.5, P7.5, Q1.S, R3.1, R8.1, R9.2, R30.2, SW1.1, TP_GND1.1, U1.4, U1.25, U2.5, U2.18, U3.2, U4.2, VR1.1

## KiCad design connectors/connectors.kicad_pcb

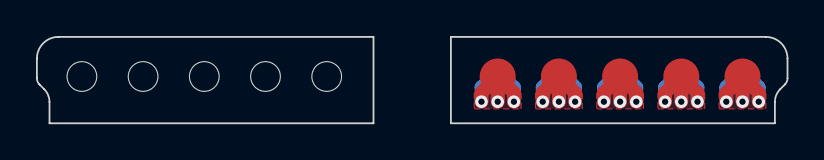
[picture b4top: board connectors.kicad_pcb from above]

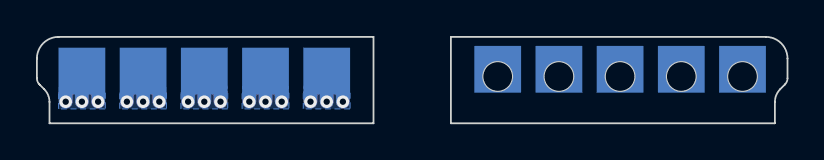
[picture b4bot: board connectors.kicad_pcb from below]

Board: 2 copper layers, 41.7 x 4.8 mm, 10 parts (5 on the bottom side), 5 nets.

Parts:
P11, P12, P13, P14, P15: CONN_1; UHK_Connector_Right_Outer_Pad
P21, P22, P23, P24, P25: CONN_1; UHK_Connector_Right_Inner_Pad

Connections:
unnamed: P11.1, P21.1
unnamed: P12.1, P22.1
unnamed: P13.1, P23.1
unnamed: P14.1, P24.1
unnamed: P15.1, P25.1

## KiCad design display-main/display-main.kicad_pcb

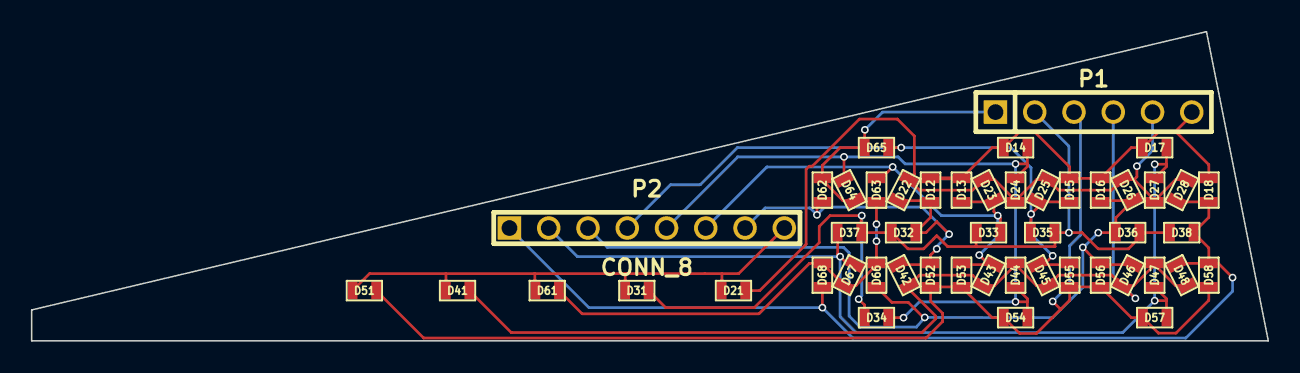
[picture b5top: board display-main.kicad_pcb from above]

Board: 2 copper layers, 80.0 x 20.0 mm, 49 parts (0 on the bottom side), 14 nets.

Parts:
D12, D13, D14, D15, D16, D17, D18, D21, D22, D23, D24, D25, D26, D27, D28, D31, D32, D33, D34, D35, D36, D37, D38, D41, D42, D43, D44, D45, D46, D47, D48, D51, D52, D53, D54, D55, D56, D57, D58, D61, D62, D63, D64, D65, D66, D67, D68: DIODE; SM0603
P1: CONN_6; PIN_ARRAY-6X1
P2: CONN_8; pin_array_8x1

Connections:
/COL1: D21.2, D31.2, D41.2, D51.2, D61.2, P2.8
/COL2: D12.2, D22.2, D32.2, D42.2, D52.2, D62.2, P2.7
/COL3: D13.2, D23.2, D33.2, D43.2, D53.2, D63.2, P2.6
/COL4: D14.2, D24.2, D34.2, D44.2, D54.2, D64.2, P2.5
/COL5: D15.2, D25.2, D35.2, D45.2, D55.2, D65.2, P2.4
/COL6: D16.2, D26.2, D36.2, D46.2, D56.2, D66.2, P2.3
/COL7: D17.2, D27.2, D37.2, D47.2, D57.2, D67.2, P2.2
/COL8: D18.2, D28.2, D38.2, D48.2, D58.2, D68.2, P2.1
/ROW1: D12.1, D13.1, D14.1, D15.1, D16.1, D17.1, D18.1, P1.6
/ROW2: D21.1, D22.1, D23.1, D24.1, D25.1, D26.1, D27.1, D28.1, P1.5
/ROW3: D31.1, D32.1, D33.1, D34.1, D35.1, D36.1, D37.1, D38.1, P1.2
/ROW4: D41.1, D42.1, D43.1, D44.1, D45.1, D46.1, D47.1, D48.1, P1.4
/ROW5: D51.1, D52.1, D53.1, D54.1, D55.1, D56.1, D57.1, D58.1, P1.3
/ROW6: D61.1, D62.1, D63.1, D64.1, D65.1, D66.1, D67.1, D68.1, P1.1
